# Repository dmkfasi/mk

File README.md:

# mk
# Redraw of arcade Mortal Kombat schematics

I actually messed up this a little bit.
The initial idea was to re-create original schematics from official arcade game manual. I started with freeware verions of
EAGLE, but then moved to KiCAD as an opensource alternative tool with no restrictions to the board size. I have completed
Sound Board only so far but never finished board layout due to high load of discrete components.

Other folders contains:
Arcade Cabinet - few FreeCAD drafts about the cabinet itself,
and
MultiKickHarness - a condenser board to hook up all the auxiliar Low Punch, Low Kick and Run buttons if you happen to have
multiple boards installed into a single cabinet.

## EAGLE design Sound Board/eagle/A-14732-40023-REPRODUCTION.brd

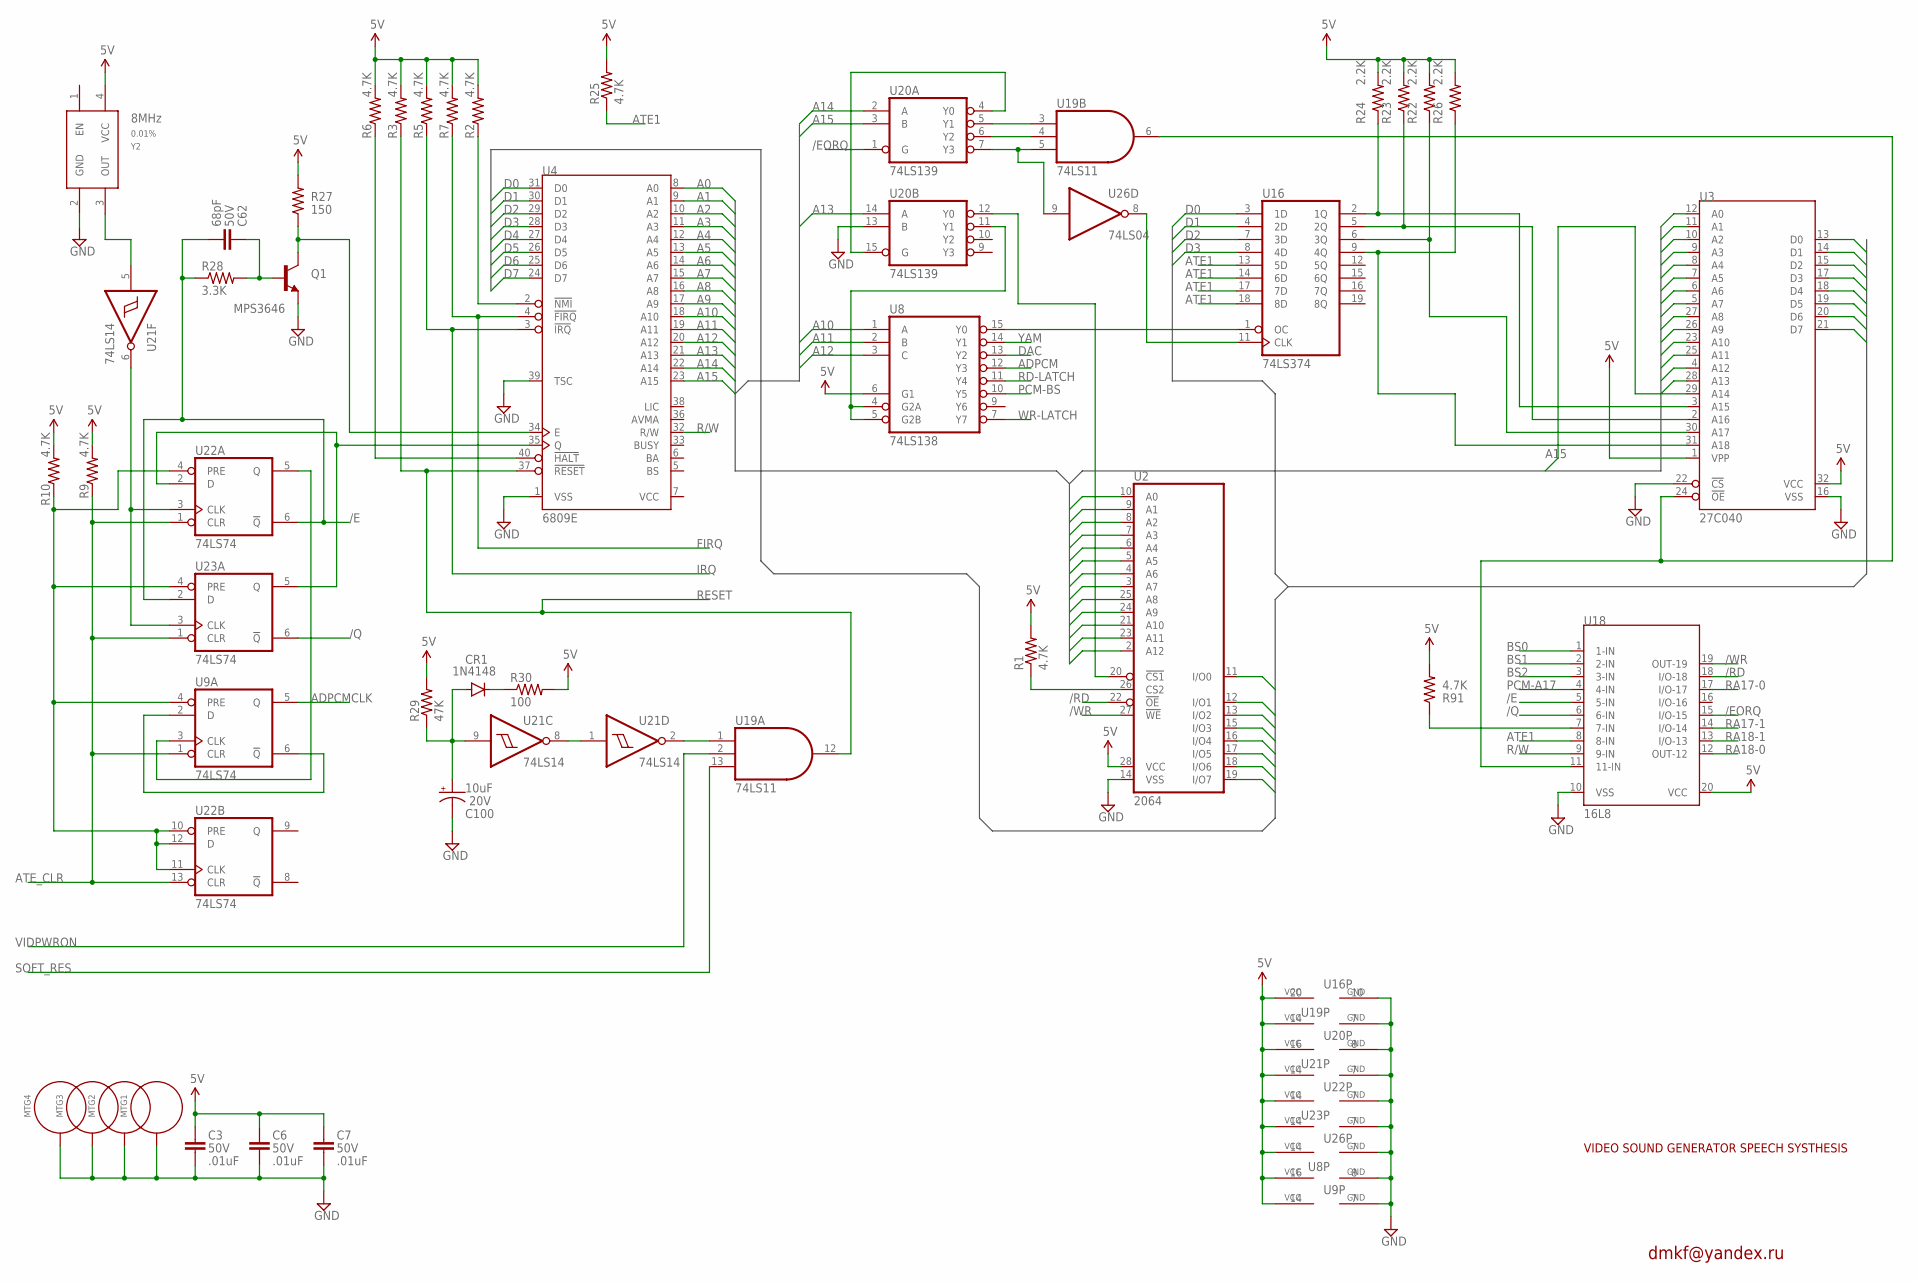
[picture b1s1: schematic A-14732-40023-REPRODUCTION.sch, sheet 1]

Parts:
C3, C6, C7: .01uF; 0805; VOLTAGE 50V
C62: 68pF; 0805
C100: 10uF; PANASONIC_C; VOLTAGE 20V
CR1: 1N4148; SMA-DIODE
MTG1, MTG2, MTG3, MTG4: MTGHOLE; STANDOFF-ELECTRICAL
Q1: MPS3646; SOT23-3
R1, R2, R3, R5, R6, R7, R9, R10, R25, R91: 4.7K; 0805
R22, R23, R24, R26: 2.2K; 0805
R27: 150; 1206
R28: 3.3K; 0805
R29: 47K; 0805
R30: 100; 1206
U2: 2064; SOP28
U3: 27C040; PLCC32R
U4: 6809E; DIP40
U8: 74LS138; SO16
U9, U22, U23: 74LS74; SO14
U16: 74LS374; SO20W
U18: 16L8; DIP20N
U19: 74LS11; SO14
U20: 74LS139; SO16
U21: 74LS14; SO14
U26: 74LS04; SO14
Y2: 8MHz; CRYSTAL-OSC-SMD-5X3; TOLERANCE 0.01%

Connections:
5V: C3.1, C6.1, C7.1, R1.2, R2.2, R3.2, R5.2, R6.2, R7.2, R9.2, R10.2, R22.2, R23.2, R24.2, R25.2, R26.2, R27.2, R29.2, R30.2, R91.2, U2.28 (VCC), U3.1 (VPP), U3.32 (VCC), U8.6 (G1), U8.16 (VCC), U9.14 (VCC), U16.20 (VCC), U18.20 (VCC), U19.14 (VCC), U20.16 (VCC), U21.14 (VCC), U22.14 (VCC), U23.14 (VCC), U26.14 (VCC), Y2.4 (VCC); also elsewhere on the board
/E: C62.1, R28.1, U18.5 (5-IN), U22.6 (!Q), U23.2 (D)
/EORQ: U18.15 (I/O-15), U20.1 (G)
/Q: U18.6 (6-IN), U23.6 (!Q)
/RD: U2.22 (!OE), U18.18 (I/O-18); also elsewhere on the board
/WR: U2.27 (!WE), U18.19 (OUT-19); also elsewhere on the board
A0: U2.10 (A0), U3.12 (A0), U4.8 (A0); also elsewhere on the board
A1: U2.9 (A1), U3.11 (A1), U4.9 (A1)
A2: U2.8 (A2), U3.10 (A2), U4.10 (A2)
A3: U2.7 (A3), U3.9 (A3), U4.11 (A3)
A4: U2.6 (A4), U3.8 (A4), U4.12 (A4)
A5: U2.5 (A5), U3.7 (A5), U4.13 (A5)
A6: U2.4 (A6), U3.6 (A6), U4.14 (A6)
A7: U2.3 (A7), U3.5 (A7), U4.15 (A7)
A8: U2.25 (A8), U3.27 (A8), U4.16 (A8)
A9: U2.24 (A9), U3.26 (A9), U4.17 (A9)
A10: U2.21 (A10), U3.23 (A10), U4.18 (A10), U8.1 (A)
A11: U2.23 (A11), U3.25 (A11), U4.19 (A11), U8.2 (B)
A12: U2.2 (A12), U3.4 (A12), U4.20 (A12), U8.3 (C)
A13: U3.28 (A13), U4.21 (A13), U20.14 (A)
A14: U4.22 (A14), U20.2 (A)
A15: U3.29 (A14), U4.23 (A15), U20.3 (B)
ADPCM: U8.12 (Y3); also elsewhere on the board
ADPCMCLK: U9.5 (Q); also elsewhere on the board
ATE1: R25.1, U16.13 (5D), U16.14 (6D), U16.17 (7D), U16.18 (8D), U18.8 (8-IN); also elsewhere on the board
ATE_CLR: R9.1, U9.1 (CLR), U22.1 (CLR), U22.13 (CLR), U23.1 (CLR); also elsewhere on the board
BS0: U18.1 (1-IN); also elsewhere on the board
BS1: U18.2 (2-IN); also elsewhere on the board
BS2: U18.3 (3-IN); also elsewhere on the board
D0: U2.11 (I/O0), U3.13 (D0), U4.31 (D0), U16.3 (1D); also elsewhere on the board
D1: U2.12 (I/O1), U3.14 (D1), U4.30 (D1), U16.4 (2D); also elsewhere on the board
D2: U2.13 (I/O2), U3.15 (D2), U4.29 (D2), U16.7 (3D); also elsewhere on the board
D3: U2.15 (I/O3), U3.17 (D3), U4.28 (D3), U16.8 (4D); also elsewhere on the board
D4: U2.16 (I/O4), U3.18 (D4), U4.27 (D4); also elsewhere on the board
D5: U2.17 (I/O5), U3.19 (D5), U4.26 (D5); also elsewhere on the board
D6: U2.18 (I/O6), U3.20 (D6), U4.25 (D6); also elsewhere on the board
D7: U2.19 (I/O7), U3.21 (D7), U4.24 (D7); also elsewhere on the board
DAC: U8.13 (Y2); also elsewhere on the board
FIRQ: R7.1, U4.4 (!FIRQ); also elsewhere on the board
GND: C3.2, C6.2, C7.2, C100.-, MTG1.P1, MTG2.P1, MTG3.P1, MTG4.P1, Q1.2 (E), U2.14 (VSS), U3.16 (VSS), U3.22 (!CS), U4.1 (VSS), U4.39 (TSC), U8.8 (GND), U9.7 (GND), U16.10 (GND), U18.10 (VSS), U19.7 (GND), U20.8 (GND), U20.13 (B), U21.7 (GND), U22.7 (GND), U23.7 (GND), U26.7 (GND), Y2.2 (GND); also elsewhere on the board
IRQ: R5.1, U4.3 (!IRQ); also elsewhere on the board
unnamed: U21.5 (I), Y2.3 (OUT)
unnamed: U21.6 (O), U22.3 (CLK), U23.3 (CLK)
unnamed: C62.2, Q1.1 (B), R28.2
unnamed: U9.3 (CLK), U22.5 (Q)
unnamed: U4.35 (Q), U22.2 (D), U23.5 (Q)
unnamed: U9.2 (D), U9.6 (!Q)
unnamed: Q1.3 (C), R27.1, U4.34 (E)
unnamed: R10.1, U9.4 (PRE), U22.4 (PRE), U22.10 (PRE), U22.11 (CLK), U22.12 (D), U23.4 (PRE)
unnamed: R6.1, U4.40 (!HALT)
unnamed: U20.4 (Y0), U20.15 (G)
unnamed: R2.1, U4.2 (!NMI)
unnamed: U8.4 (G2A), U8.5 (G2B), U20.11 (Y1)
unnamed: U19.3 (I0), U20.5 (Y1)
unnamed: C100.+, CR1.A, R29.1, U21.9 (I)
unnamed: CR1.C, R30.1
unnamed: U21.1 (I), U21.8 (O)
unnamed: U19.4 (I1), U20.6 (Y2)
unnamed: U19.5 (I2), U20.7 (Y3), U26.9 (I)
unnamed: U19.1 (I0), U21.2 (O)
unnamed: U8.15 (Y0), U16.1 (OC)
unnamed: U16.11 (CLK), U26.8 (O)
unnamed: U2.20 (!CS1), U20.12 (Y0)
unnamed: R1.1, U2.26 (CS2)
unnamed: U3.24 (!OE), U18.11 (11-IN), U19.6 (O)
unnamed: R24.1, U3.3 (A15), U16.2 (1Q)
unnamed: R23.1, U3.2 (A16), U16.5 (2Q)
unnamed: R22.1, U3.30 (A17), U16.6 (3Q)
unnamed: R26.1, U3.31 (A18), U16.9 (4Q)
unnamed: R91.1, U18.7 (7-IN)
PCM-A17: U18.4 (4-IN); also elsewhere on the board
PCM-BS: U8.10 (Y5); also elsewhere on the board
R/W: U4.32 (R/W), U18.9 (9-IN)
RA17-0: U18.17 (I/O-17); also elsewhere on the board
RA17-1: U18.14 (I/O-14); also elsewhere on the board
RA18-0: U18.12 (OUT-12); also elsewhere on the board
RA18-1: U18.13 (I/O-13); also elsewhere on the board
RD-LATCH: U8.11 (Y4); also elsewhere on the board
RESET: R3.1, U4.37 (!RESET), U19.12 (O); also elsewhere on the board
SOFT_RES: U19.13 (I2); also elsewhere on the board
VIDPWRON: U19.2 (I1); also elsewhere on the board
WR-LATCH: U8.7 (Y7); also elsewhere on the board
YAM: U8.14 (Y1); also elsewhere on the board

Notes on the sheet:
VIDEO SOUND GENERATOR SPEECH SYSTHESIS
dmkf@yandex.ru

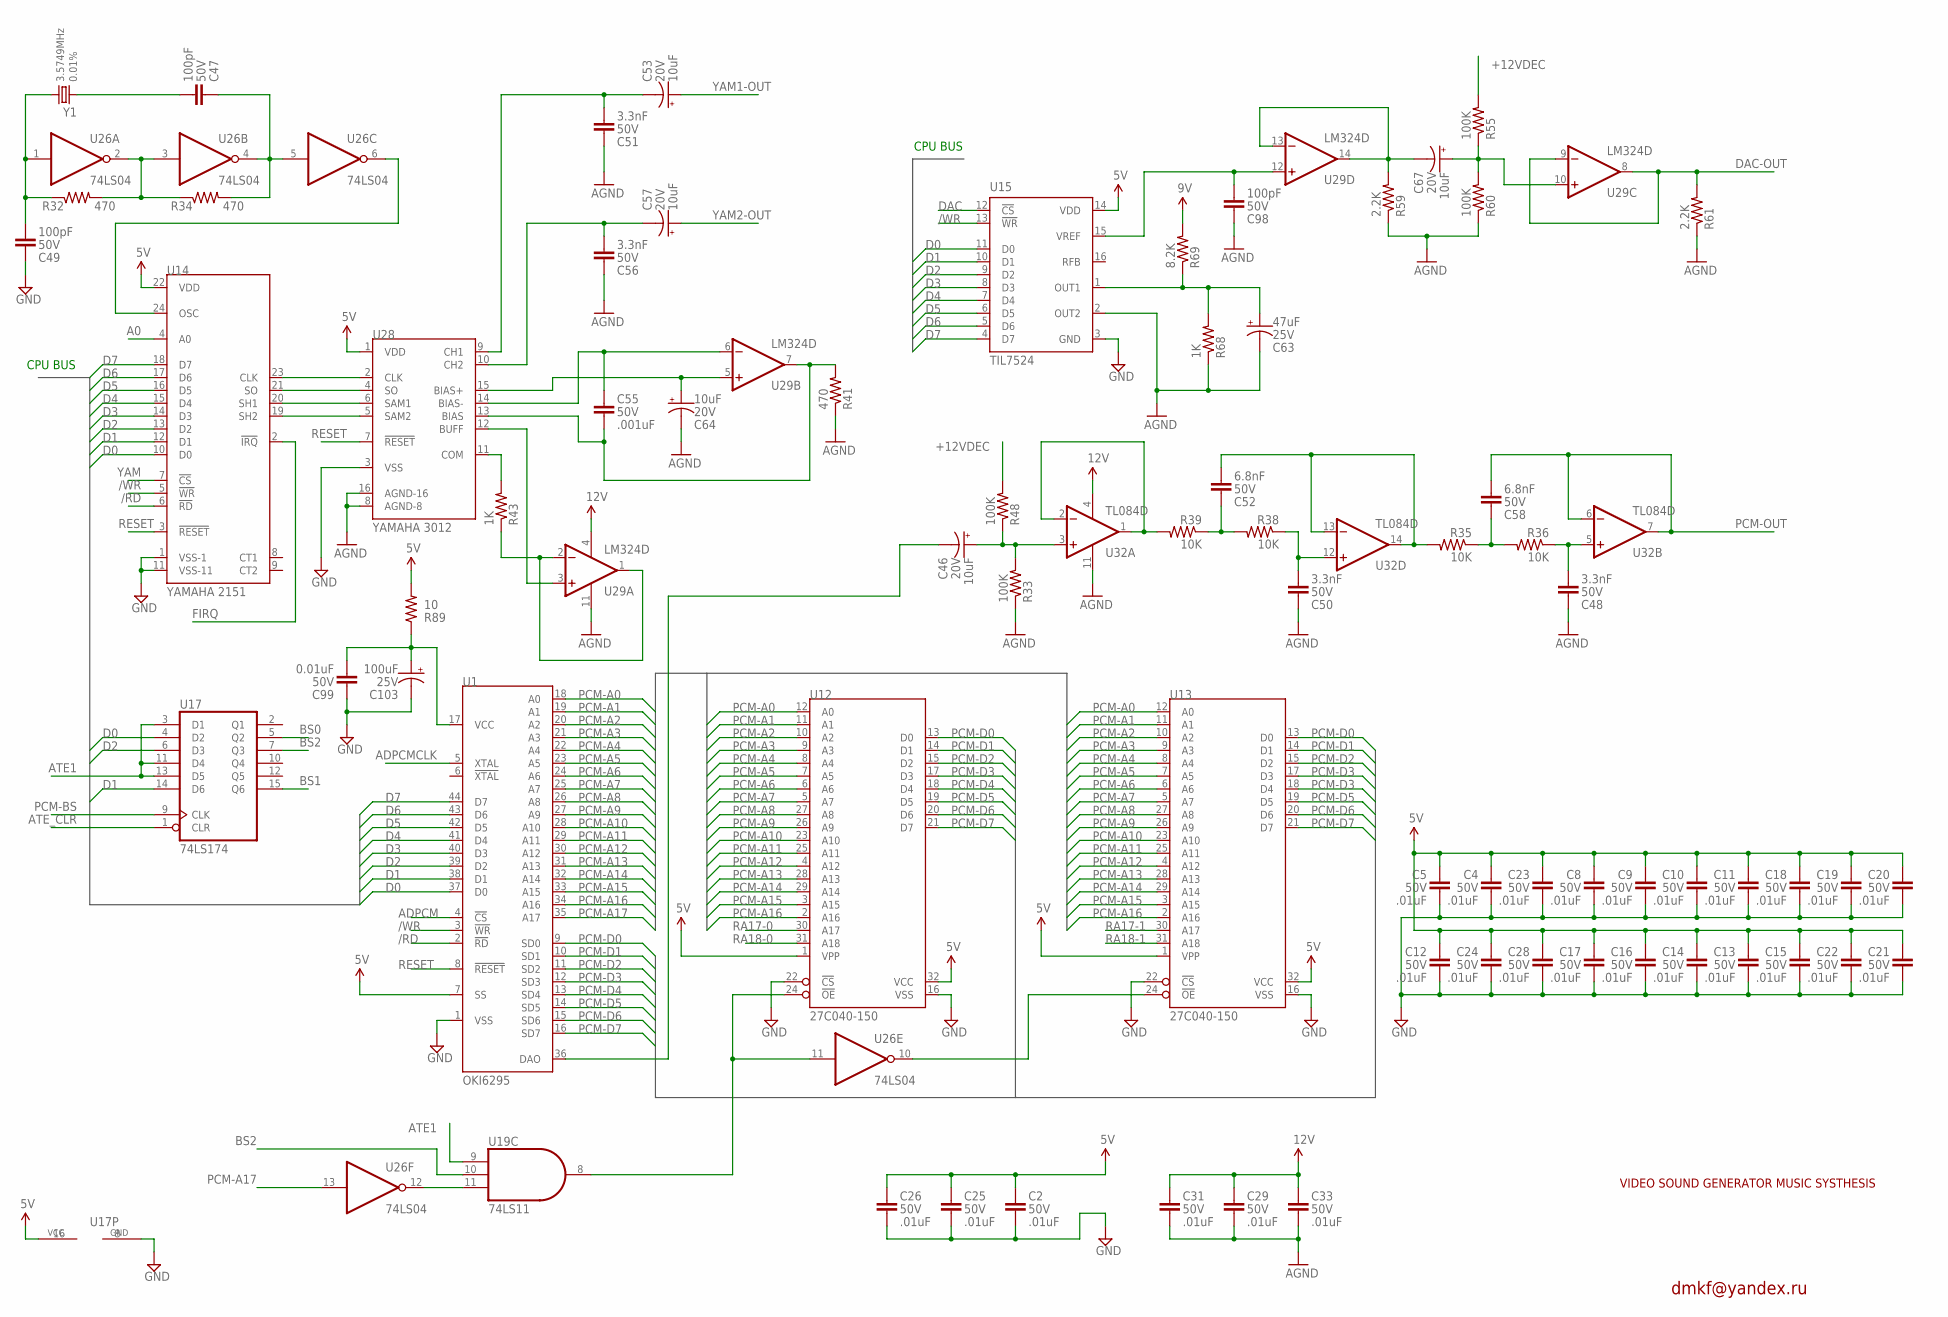
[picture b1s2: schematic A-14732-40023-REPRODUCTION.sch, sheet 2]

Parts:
C2, C4, C5, C8, C9, C10, C11, C12, C13, C14, C15, C16, C17, C18, C19, C20, C21, C22, C23, C24, C25, C26, C28, C29, C31, C33: .01uF; 0805; VOLTAGE 50V
C46, C53, C57, C64, C67: 10uF; PANASONIC_C; VOLTAGE 20V
C47, C49, C98: 100pF; 0805; VOLTAGE 50V
C48, C50, C51, C56: 3.3nF; 0805; VOLTAGE 50V
C52, C58: 6.8nF; 0805; VOLTAGE 50V
C55: .001uF; 0805; VOLTAGE 50V
C63: 47uF; PANASONIC_D; VOLTAGE 25V
C99: 0.01uF; 0805; VOLTAGE 50V
C103: 100uF; PANASONIC_D; VOLTAGE 25V
R32, R34, R41: 470; 0805
R33, R48, R55, R60: 100K; 0805
R35, R36, R38, R39: 10K; 0805
R43, R68: 1K; 0805
R59, R61: 2.2K; 0805
R69: 8.2K; 0805
R89: 10; 1206
U1: OKI6295; QFP44
U12, U13: 27C040-150; PLCC32R
U14: YAMAHA 2151; DIP24
U15: TIL7524; SOIC16N
U17: 74LS174; SO16
U19: 74LS11; SO14
U26: 74LS04; SO14
U28: YAMAHA 3012; DIP16N
U29: LM324D; SO14
U32: TL084D; SO14
Y1: 3.5749MHz; HC49UP; TOLERANCE 0.01%

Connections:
5V: C2.1, C4.1, C5.1, C8.1, C9.1, C10.1, C11.1, C12.1, C13.1, C14.1, C15.1, C16.1, C17.1, C18.1, C19.1, C20.1, C21.1, C22.1, C23.1, C24.1, C25.1, C26.1, C28.1, R69.2, R89.2, U1.7 (SS), U12.1 (VPP), U12.32 (VCC), U13.1 (VPP), U13.32 (VCC), U14.22 (VDD), U15.14 (VDD), U17.16 (VCC), U28.1 (VDD); also elsewhere on the board
12V: C29.1, C31.1, C33.1, U29.4 (V+), U32.4 (V+); also elsewhere on the board
+12VDEC: R48.2, R55.2; also elsewhere on the board
/RD: U1.2 (!RD), U14.6 (!RD); also elsewhere on the board
/WR: U1.3 (!WR), U14.5 (!WR), U15.13 (!WR); also elsewhere on the board
A0: U14.4 (A0); also elsewhere on the board
ADPCM: U1.4 (!CS); also elsewhere on the board
ADPCMCLK: U1.5 (XTAL); also elsewhere on the board
AGND: C29.2, C31.2, C33.2, C48.2, C50.2, C51.2, C56.2, C63.-, C64.-, C98.2, R33.1, R41.1, R59.1, R60.1, R61.1, R68.1, U15.2 (OUT2), U28.8 (AGND-8), U28.16 (AGND-16), U29.11 (V-), U32.11 (V-); also elsewhere on the board
ATE1: U17.3 (D1), U17.11 (D4), U17.13 (D5), U19.9 (I0); also elsewhere on the board
ATE_CLR: U17.1 (CLR); also elsewhere on the board
BS0: U17.5 (Q2); also elsewhere on the board
BS1: U17.15 (Q6); also elsewhere on the board
BS2: U17.7 (Q3), U19.10 (I1); also elsewhere on the board
D0: U1.37 (D0), U14.10 (D0), U15.11 (D0), U17.4 (D2); also elsewhere on the board
D1: U1.38 (D1), U14.12 (D1), U15.10 (D1), U17.14 (D6); also elsewhere on the board
D2: U1.39 (D2), U14.13 (D2), U15.9 (D2), U17.6 (D3); also elsewhere on the board
D3: U1.40 (D3), U14.14 (D3), U15.8 (D3); also elsewhere on the board
D4: U1.41 (D4), U14.15 (D4), U15.7 (D4); also elsewhere on the board
D5: U1.42 (D5), U14.16 (D5), U15.6 (D5); also elsewhere on the board
D6: U1.43 (D6), U14.17 (D6), U15.5 (D6); also elsewhere on the board
D7: U1.44 (D7), U14.18 (D7), U15.4 (D7); also elsewhere on the board
DAC: U15.12 (!CS); also elsewhere on the board
DAC-OUT: R61.2, U29.8 (OUT), U29.9 (-IN); also elsewhere on the board
FIRQ: U14.2 (!IRQ); also elsewhere on the board
GND: C2.2, C4.2, C5.2, C8.2, C9.2, C10.2, C11.2, C12.2, C13.2, C14.2, C15.2, C16.2, C17.2, C18.2, C19.2, C20.2, C21.2, C22.2, C23.2, C24.2, C25.2, C26.2, C28.2, C49.2, C99.2, C103.-, U1.1 (VSS), U12.16 (VSS), U12.22 (!CS), U13.16 (VSS), U13.22 (!CS), U14.1 (VSS-1), U14.11 (VSS-11), U15.3 (GND), U17.8 (GND), U28.3 (VSS); also elsewhere on the board
unnamed: C49.1, R32.1, U26.1 (I), Y1.1
unnamed: R32.2, R34.1, U26.2 (O), U26.3 (I)
unnamed: C47.2, R34.2, U26.4 (O), U26.5 (I)
unnamed: C47.1, Y1.2
unnamed: U14.24 (OSC), U26.6 (O)
unnamed: U14.23 (CLK), U28.2 (CLK)
unnamed: U14.21 (SO), U28.4 (SO)
unnamed: U14.20 (SH1), U28.6 (SAM1)
unnamed: U14.19 (SH2), U28.5 (SAM2)
unnamed: C99.1, C103.+, R89.1, U1.17 (VCC)
unnamed: U19.11 (I2), U26.12 (O)
unnamed: U12.24 (!OE), U19.8 (O), U26.11 (I)
unnamed: U13.24 (!OE), U26.10 (O)
unnamed: C46.-, U1.36 (DAO)
unnamed: C51.1, C53.-, U28.9 (CH1)
unnamed: C56.1, C57.-, U28.10 (CH2)
unnamed: R43.1, U29.1 (OUT), U29.2 (-IN)
unnamed: R43.2, U28.11 (COM)
unnamed: U28.12 (BUFF), U29.3 (+IN)
unnamed: C55.2, R41.2, U28.13 (BIAS), U29.7 (OUT)
unnamed: C55.1, U28.14 (BIAS-), U29.6 (-IN)
unnamed: C63.+, R68.2, R69.1, U15.1 (OUT1)
unnamed: C64.+, U28.15 (BIAS+), U29.5 (+IN)
unnamed: C98.1, U15.15 (VREF), U29.12 (+IN)
unnamed: C67.-, R59.2, U29.13 (-IN), U29.14 (OUT)
unnamed: C67.+, R55.1, R60.2, U29.10 (+IN)
unnamed: C46.+, R33.2, R48.1, U32.3 (+IN)
unnamed: R39.2, U32.1 (OUT), U32.2 (-IN)
unnamed: C52.2, R38.2, R39.1
unnamed: C52.1, R35.2, U32.13 (-IN), U32.14 (OUT)
unnamed: C50.1, R38.1, U32.12 (+IN)
unnamed: C58.2, R35.1, R36.2
unnamed: C48.1, R36.1, U32.5 (+IN)
PCM-A0: U1.18 (A0), U12.12 (A0), U13.12 (A0)
PCM-A1: U1.19 (A1), U12.11 (A1), U13.11 (A1)
PCM-A2: U1.20 (A2), U12.10 (A2), U13.10 (A2)
PCM-A3: U1.21 (A3), U12.9 (A3), U13.9 (A3)
PCM-A4: U1.22 (A4), U12.8 (A4), U13.8 (A4)
PCM-A5: U1.23 (A5), U12.7 (A5), U13.7 (A5)
PCM-A6: U1.24 (A6), U12.6 (A6), U13.6 (A6)
PCM-A7: U1.25 (A7), U12.5 (A7), U13.5 (A7)
PCM-A8: U1.26 (A8), U12.27 (A8), U13.27 (A8)
PCM-A9: U1.27 (A9), U12.26 (A9), U13.26 (A9)
PCM-A10: U1.28 (A10), U12.23 (A10), U13.23 (A10)
PCM-A11: U1.29 (A11), U12.25 (A11), U13.25 (A11)
PCM-A12: U1.30 (A12), U12.4 (A12), U13.4 (A12)
PCM-A13: U1.31 (A13), U12.28 (A13), U13.28 (A13)
PCM-A14: U1.32 (A14), U12.29 (A14), U13.29 (A14)
PCM-A15: U1.33 (A15), U12.3 (A15), U13.3 (A15)
PCM-A16: U1.34 (A16), U12.2 (A16), U13.2 (A16)
PCM-A17: U1.35 (A17), U26.13 (I); also elsewhere on the board
PCM-BS: U17.9 (CLK); also elsewhere on the board
PCM-D0: U1.9 (SD0), U12.13 (D0), U13.13 (D0)
PCM-D1: U1.10 (SD1), U12.14 (D1), U13.14 (D1)
PCM-D2: U1.11 (SD2), U12.15 (D2), U13.15 (D2)
PCM-D3: U1.12 (SD3), U12.17 (D3), U13.17 (D3), U13.18 (D4)
PCM-D4: U1.13 (SD4), U12.18 (D4)
PCM-D5: U1.14 (SD5), U12.19 (D5), U13.19 (D5)
PCM-D6: U1.15 (SD6), U12.20 (D6), U13.20 (D6)
PCM-D7: U1.16 (SD7), U12.21 (D7), U13.21 (D7)
PCM-OUT: C58.1, U32.6 (-IN), U32.7 (OUT); also elsewhere on the board
RA17-0: U12.30 (A17); also elsewhere on the board
RA17-1: U13.30 (A17); also elsewhere on the board
RA18-0: U12.31 (A18); also elsewhere on the board
RA18-1: U13.31 (A18); also elsewhere on the board
RESET: U1.8 (!RESET), U14.3 (!RESET), U28.7 (!RESET); also elsewhere on the board
YAM: U14.7 (!CS); also elsewhere on the board
YAM1-OUT: C53.+; also elsewhere on the board
YAM2-OUT: C57.+; also elsewhere on the board

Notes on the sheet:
dmkf@yandex.ru
VIDEO SOUND GENERATOR MUSIC SYSTHESIS
CPU BUS

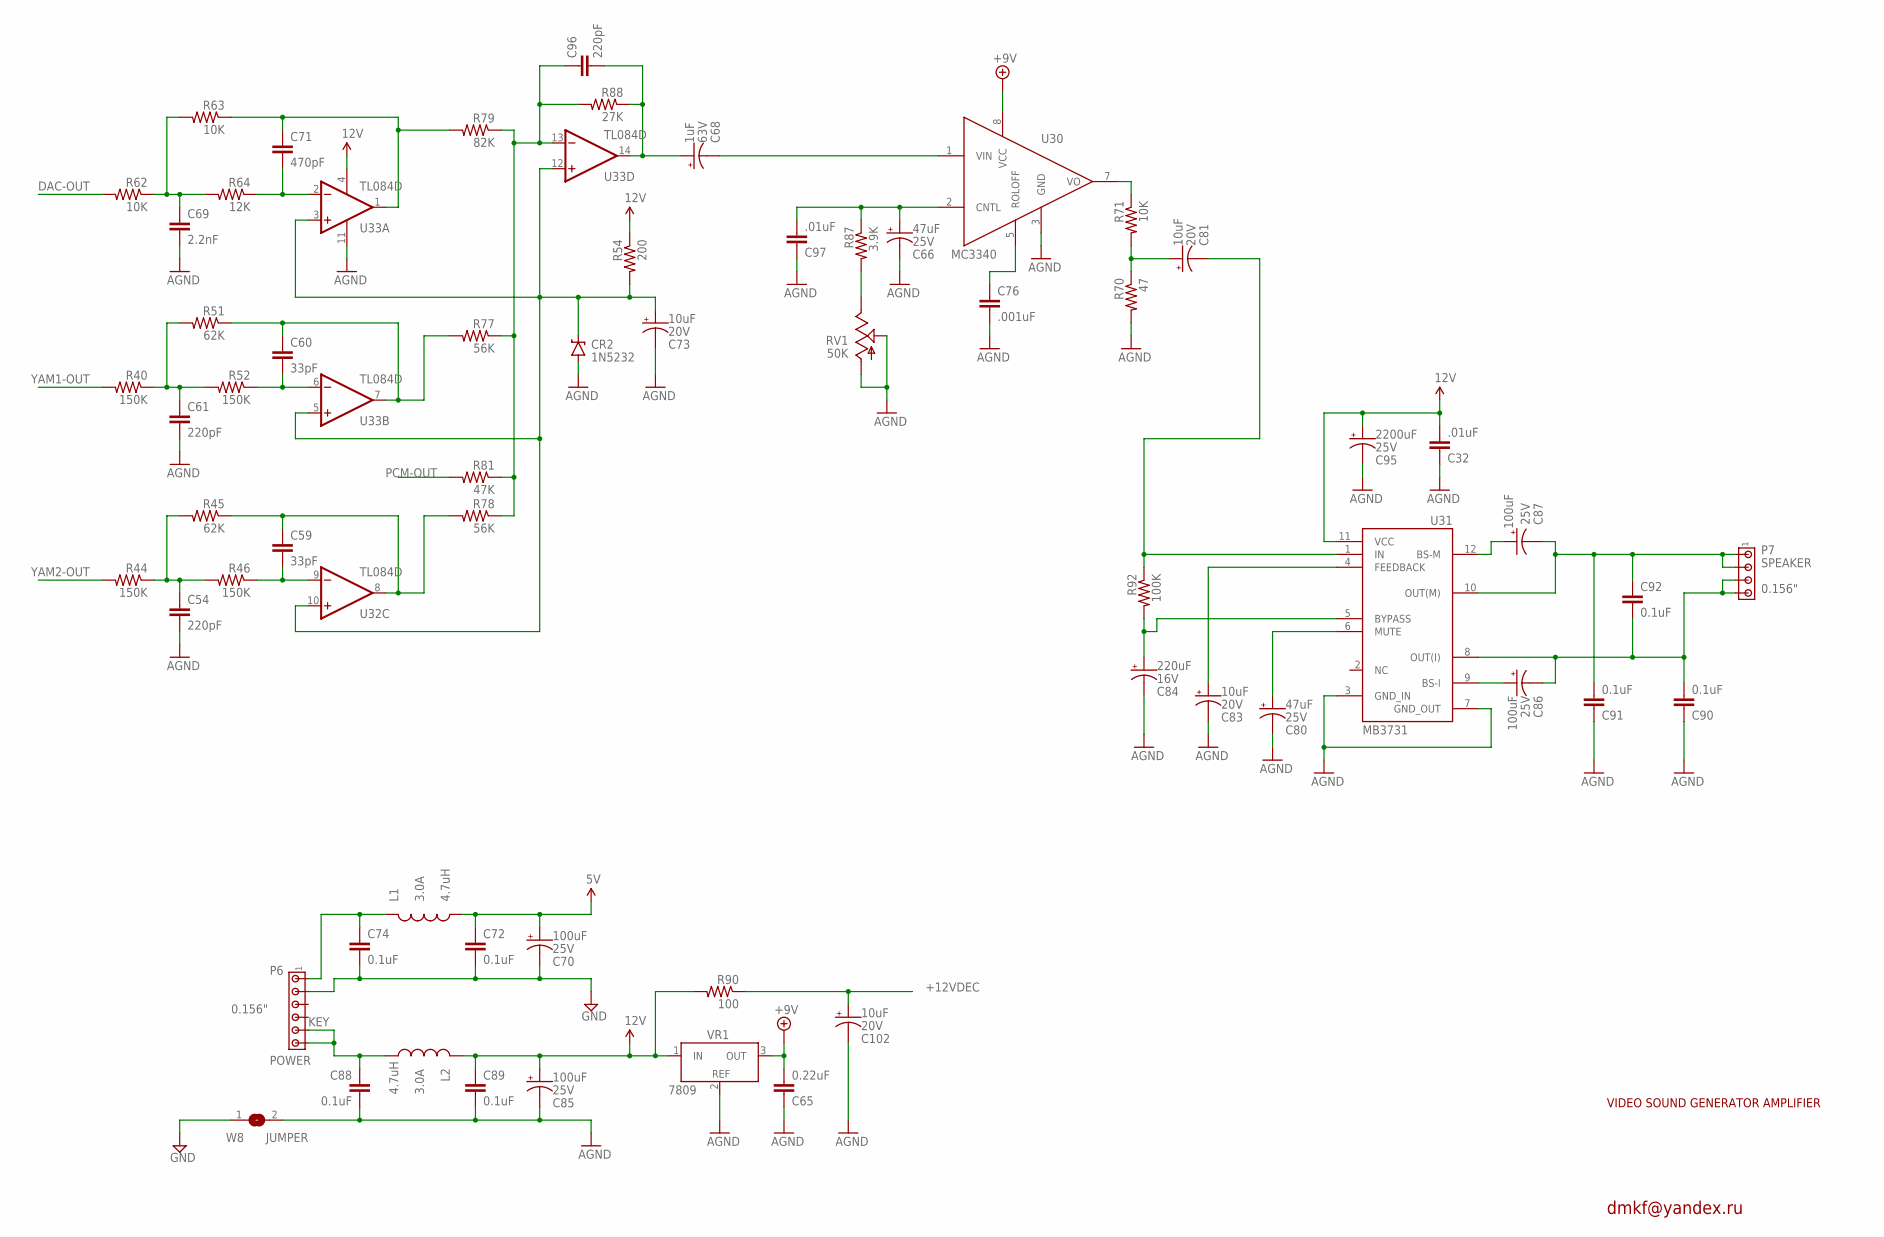
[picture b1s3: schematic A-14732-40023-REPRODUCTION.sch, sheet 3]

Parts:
C32, C97: .01uF; 0805; VOLTAGE 50V
C54, C61, C96: 220pF; 0805; VOLTAGE 50V
C59, C60: 33pF; 0805; VOLTAGE 50V
C65: 0.22uF; 0805; VOLTAGE 50V
C66, C80: 47uF; PANASONIC_D; VOLTAGE 25V
C68: 1uF; PANASONIC_C; VOLTAGE 63V
C69: 2.2nF; 0805; VOLTAGE 50V
C70, C85, C86, C87: 100uF; PANASONIC_D; VOLTAGE 25V
C71: 470pF; 0805; VOLTAGE 50V
C72, C74, C88, C89, C90, C91, C92: 0.1uF; 0805; VOLTAGE 50V
C73, C81, C83, C102: 10uF; PANASONIC_C; VOLTAGE 20V
C76: .001uF; 0805; VOLTAGE 50V
C84: 220uF; PANASONIC_E; VOLTAGE 16V
C95: 2200uF; CPOL-RADIAL-1000UF-25V; VOLTAGE 25V
CR2: 1N5232; SOT23
L1, L2: 4.7uH; NPI75C
P6: POWER; 1X6MTA
P7: SPEAKER; 1X4MTA
R40, R44, R46, R52: 150K; 0805
R45, R51: 62K; 0805
R54: 200; R1206
R62, R63, R71: 10K; 0805
R64: 12K; 0805
R70: 47; R1206
R77, R78: 56K; 0805
R79: 82K; 0805
R81: 47K; 0805
R87: 3.9K; 0805
R88: 27K; 0805
R90: 100; R1206
R92: 100K; 0805
RV1: 50K; POT_ALPHA_RV16AF-20
U30: MC3340
U31: MB3731; SIP12
U32, U33: TL084D; SO14
VR1: 7809; 7809-TO220V; PARTNUMBER 5460-12743-00
W8: JUMPER; SJ

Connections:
5V: C70.+, C72.1, L1.1; also elsewhere on the board
12V: C32.2, C85.+, C89.1, C95.1 (+), L2.2, R54.1, R90.2, U31.11 (VCC), U33.4 (V+), VR1.1 (IN); also elsewhere on the board
+9V: C65.2, U30.8 (VCC), VR1.3 (OUT)
+12VDEC: C102.+, R90.1; also elsewhere on the board
AGND: C32.1, C54.2, C61.2, C65.1, C66.-, C69.2, C73.-, C76.2, C80.-, C83.-, C84.-, C85.-, C88.2, C89.2, C90.1, C91.1, C95.2 (-), C97.1, C102.-, CR2.1 (A), R70.2, RV1.1 (A), RV1.2 (S), U30.3 (GND), U31.3 (GND_IN), U31.7 (GND_OUT), U33.11 (V-), VR1.2 (REF), W8.2; also elsewhere on the board
DAC-OUT: R62.2; also elsewhere on the board
GND: C70.-, C72.2, C74.2, P6.2, W8.1; also elsewhere on the board
unnamed: C73.+, CR2.3 (C), R54.2, U32.10 (+IN), U33.3 (+IN), U33.5 (+IN), U33.12 (+IN)
unnamed: C74.1, L1.2, P6.1
unnamed: C68.-, U30.1 (VIN)
unnamed: C69.1, R62.1, R63.2, R64.2
unnamed: C71.2, R64.1, U33.2 (-IN)
unnamed: C71.1, R63.1, R79.2, U33.1 (OUT)
unnamed: C60.1, R51.1, R77.2, U33.7 (OUT)
unnamed: C61.1, R40.1, R51.2, R52.2
unnamed: C60.2, R52.1, U33.6 (-IN)
unnamed: C96.1, R77.1, R78.1, R79.1, R81.1, R88.2, U33.13 (-IN)
unnamed: C54.1, R44.1, R45.2, R46.2
unnamed: C59.1, R45.1, R78.2, U32.8 (OUT)
unnamed: C59.2, R46.1, U32.9 (-IN)
unnamed: C68.+, C96.2, R88.1, U33.14 (OUT)
unnamed: C88.1, L2.1, P6.5, P6.6
unnamed: C66.+, C97.2, R87.1, U30.2 (CNTL)
unnamed: R87.2, RV1.3 (E)
unnamed: C76.1, U30.5 (ROLOFF)
unnamed: C81.+, R70.1, R71.2
unnamed: R71.1, U30.7 (VO)
unnamed: C81.-, R92.1, U31.1 (IN)
unnamed: C84.+, R92.2, U31.5 (BYPASS)
unnamed: C83.+, U31.4 (FEEDBACK)
unnamed: C80.+, U31.6 (MUTE)
unnamed: C87.+, U31.12 (BS-M)
unnamed: C86.+, U31.9 (BS-I)
unnamed: C87.-, C91.2, C92.1, P7.1, P7.2, U31.10 (OUT(M))
unnamed: C86.-, C90.2, C92.2, P7.3, P7.4, U31.8 (OUT(I))
PCM-OUT: R81.2; also elsewhere on the board
YAM1-OUT: R40.2; also elsewhere on the board
YAM2-OUT: R44.2; also elsewhere on the board

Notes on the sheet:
VIDEO SOUND GENERATOR AMPLIFIER
dmkf@yandex.ru

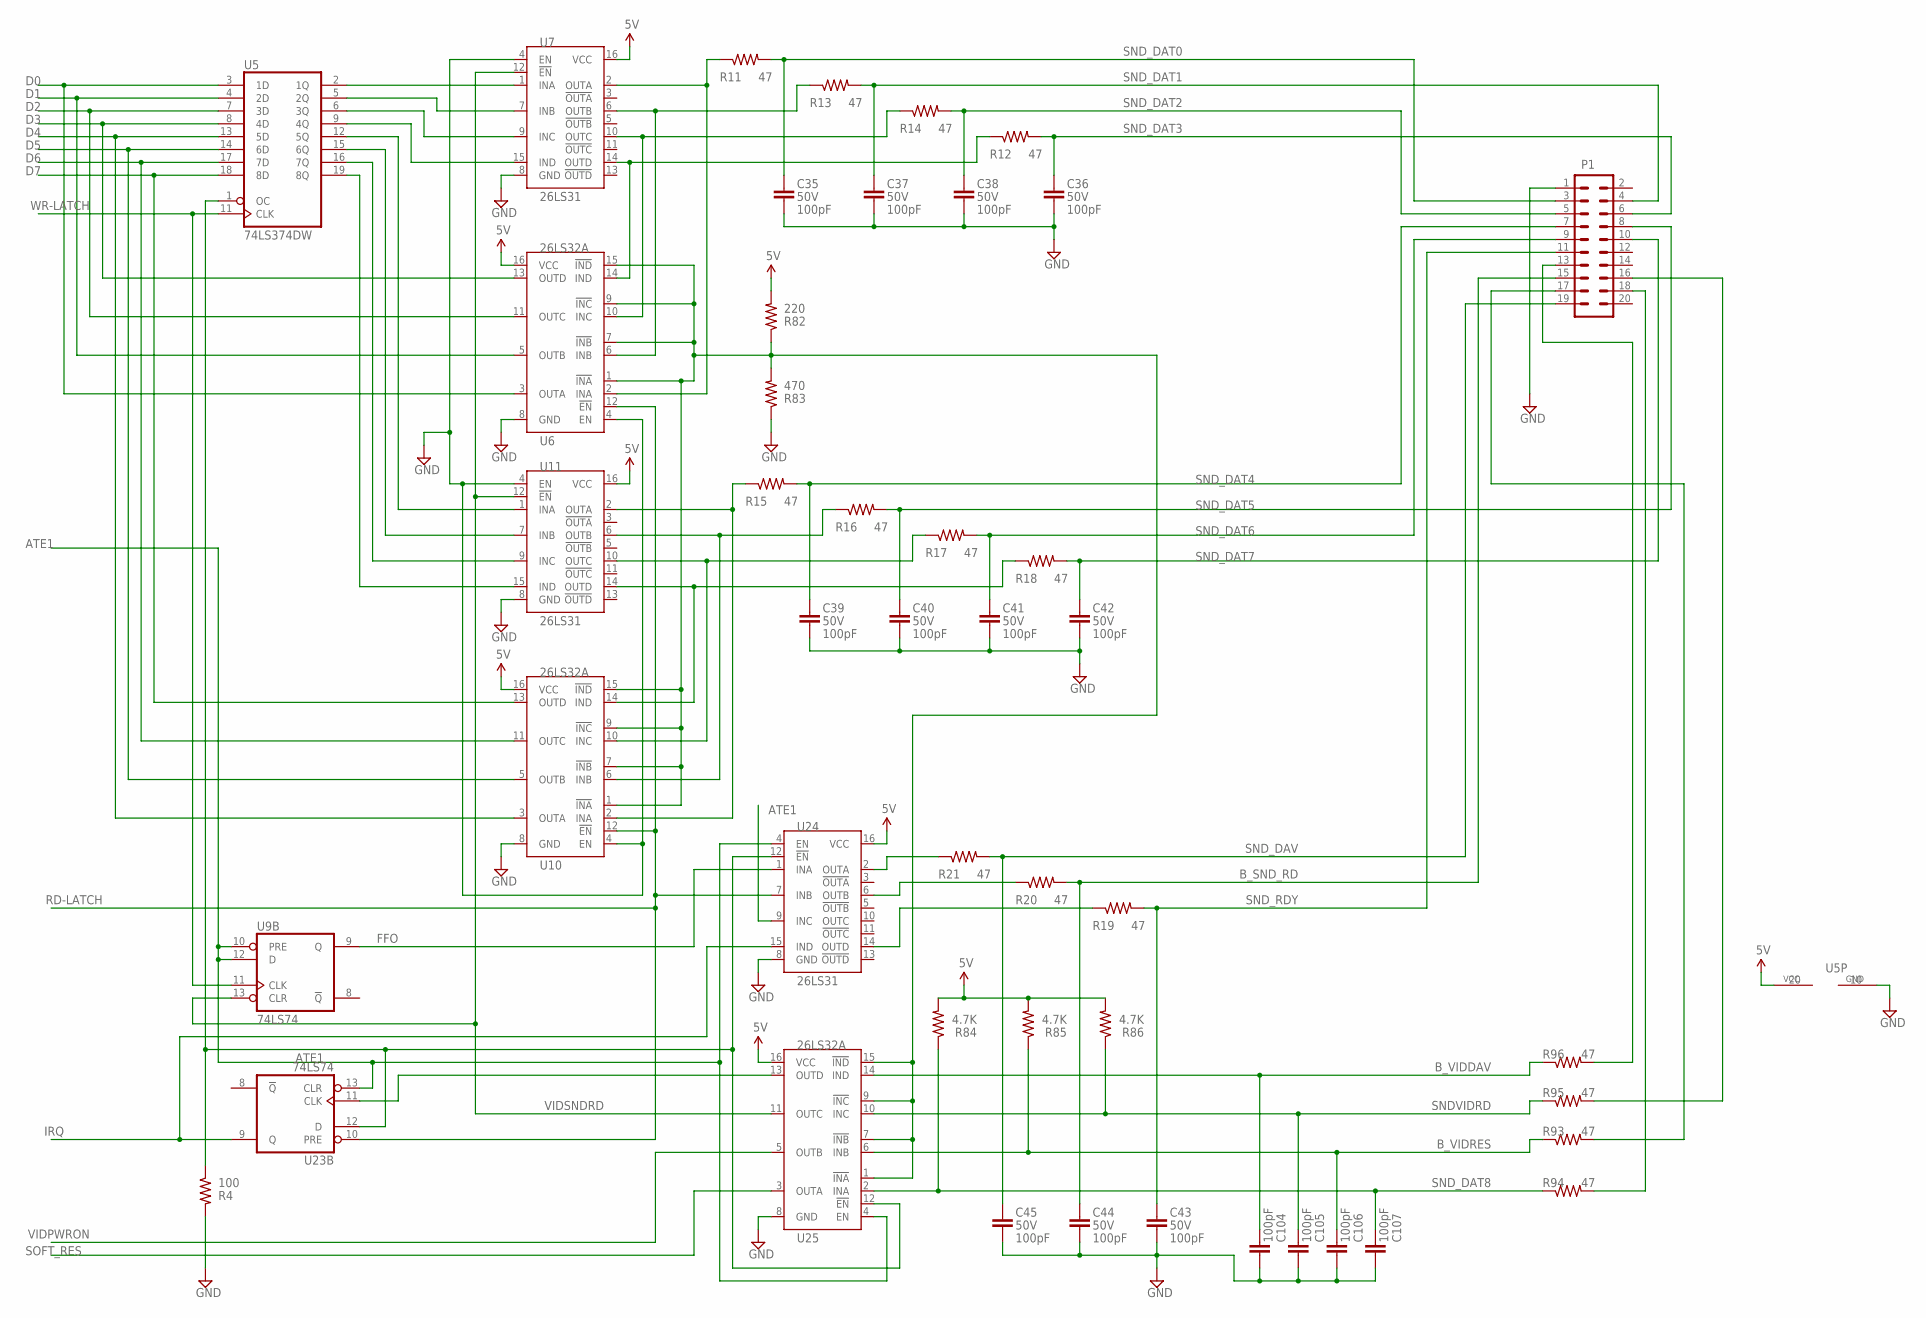
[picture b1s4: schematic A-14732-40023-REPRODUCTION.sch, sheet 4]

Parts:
C35, C36, C37, C38, C39, C40, C41, C42, C43, C44, C45, C104, C105, C106, C107: 100pF; 0805; VOLTAGE 50V
P1: M10X2ROUND_NOSILK; 2X10_ROUND_NOSILK
R4: 100; 0805
R11, R12, R13, R14, R15, R16, R17, R18, R19, R20, R21, R93, R94, R95, R96: 47; 0805
R82: 220; R1206
R83: 470; R1206
R84, R85, R86: 4.7K; 0805
U5: 74LS374DW; SO20W
U6, U10, U25: 26LS32A; SO16
U7, U11, U24: 26LS31; SO16
U9, U23: 74LS74; SO14

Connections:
5V: R82.2, R84.2, R85.2, R86.2, U5.20 (VCC), U6.16 (VCC), U7.16 (VCC), U10.16 (VCC), U11.16 (VCC), U24.16 (VCC), U25.16 (VCC); also elsewhere on the board
ATE1: U9.10 (PRE), U9.12 (D), U23.13 (CLR), U24.4 (EN), U24.9 (INC), U25.4 (EN); also elsewhere on the board
B_SND_RD: C44.1, P1.15, R20.2
B_VIDDAV: C104.2, R96.1, U25.14 (IND)
B_VIDRES: C106.1, R85.1, R93.1, U25.6 (INB)
D0: U5.3 (1D), U6.3 (OUTA); also elsewhere on the board
D1: U5.4 (2D), U6.5 (OUTB); also elsewhere on the board
D2: U5.7 (3D), U6.11 (OUTC); also elsewhere on the board
D3: U5.8 (4D), U6.13 (OUTD); also elsewhere on the board
D4: U5.13 (5D), U10.3 (OUTA); also elsewhere on the board
D5: U5.14 (6D), U10.5 (OUTB); also elsewhere on the board
D6: U5.17 (7D), U10.11 (OUTC); also elsewhere on the board
D7: U5.18 (8D), U10.13 (OUTD); also elsewhere on the board
FFO: U9.9 (Q), U24.1 (INA)
GND: C35.2, C36.2, C37.2, C38.2, C39.2, C40.2, C41.2, C42.2, C43.2, C44.2, C45.2, C104.1, C105.1, C106.2, C107.2, P1.1, R4.2, R83.1, U5.10 (GND), U6.4 (EN), U6.8 (GND), U7.4 (EN), U7.8 (GND), U10.4 (EN), U10.8 (GND), U11.4 (EN), U11.8 (GND), U24.8 (GND), U25.8 (GND); also elsewhere on the board
IRQ: U23.9 (Q), U24.15 (IND); also elsewhere on the board
unnamed: P1.13, R96.2
unnamed: U5.2 (1Q), U7.1 (INA)
unnamed: P1.16, R95.2
unnamed: P1.17, R93.2
unnamed: P1.18, R94.2
unnamed: U5.5 (2Q), U7.7 (INB)
unnamed: U5.6 (3Q), U7.9 (INC)
unnamed: U5.9 (4Q), U7.15 (IND)
unnamed: U5.12 (5Q), U11.1 (INA)
unnamed: U5.15 (6Q), U11.7 (INB)
unnamed: U5.16 (7Q), U11.9 (INC)
unnamed: U5.19 (8Q), U11.15 (IND)
unnamed: R21.1, U24.2 (OUTA)
unnamed: R15.1, U10.2 (INA), U11.2 (OUTA)
unnamed: U23.11 (CLK), U25.13 (OUTD)
unnamed: R4.1, U5.1 (OC), U23.12 (D), U24.12 (!EN), U25.12 (!EN)
unnamed: R11.1, U6.2 (INA), U7.2 (OUTA)
unnamed: R16.1, U10.6 (INB), U11.6 (OUTB)
unnamed: R13.1, U6.6 (INB), U7.6 (OUTB)
unnamed: R17.1, U10.10 (INC), U11.10 (OUTC)
unnamed: R18.1, U10.14 (IND), U11.14 (OUTD)
unnamed: R82.1, R83.2, U6.1 (!INA), U6.7 (!INB), U6.9 (!INC), U6.15 (!IND), U10.1 (!INA), U10.7 (!INB), U10.9 (!INC), U10.15 (!IND), U25.1 (!INA), U25.7 (!INB), U25.9 (!INC), U25.15 (!IND)
unnamed: R14.1, U6.10 (INC), U7.10 (OUTC)
unnamed: R12.1, U6.14 (IND), U7.14 (OUTD)
unnamed: R20.1, U24.6 (OUTB)
unnamed: R19.1, U24.14 (OUTD)
RD-LATCH: U6.12 (!EN), U10.12 (!EN), U23.10 (PRE), U24.7 (INB); also elsewhere on the board
SNDVIDRD: C105.2, R86.1, R95.1, U25.10 (INC)
SND_DAT0: C35.1, P1.3, R11.2
SND_DAT1: C37.1, P1.4, R13.2
SND_DAT2: C38.1, P1.5, R14.2
SND_DAT3: C36.1, P1.6, R12.2
SND_DAT4: C39.1, P1.7, R15.2
SND_DAT5: C40.1, P1.8, R16.2
SND_DAT6: C41.1, P1.9, R17.2
SND_DAT7: C42.1, P1.10, R18.2
SND_DAT8: C107.1, R84.1, R94.1, U25.2 (INA)
SND_DAV: C45.1, P1.19, R21.2
SND_RDY: C43.1, P1.11, R19.2
SOFT_RES: U25.3 (OUTA); also elsewhere on the board
VIDPWRON: U25.5 (OUTB); also elsewhere on the board
VIDSNDRD: U7.12 (!EN), U9.13 (CLR), U11.12 (!EN), U25.11 (OUTC)
WR-LATCH: U5.11 (CLK), U9.11 (CLK); also elsewhere on the board

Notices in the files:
parts and their libraries:
SparkFun-Aesthetics: Licensing: Creative Commons ShareAlike 4.0 International - https://creativecommons.org/licenses/by-sa/4.0
